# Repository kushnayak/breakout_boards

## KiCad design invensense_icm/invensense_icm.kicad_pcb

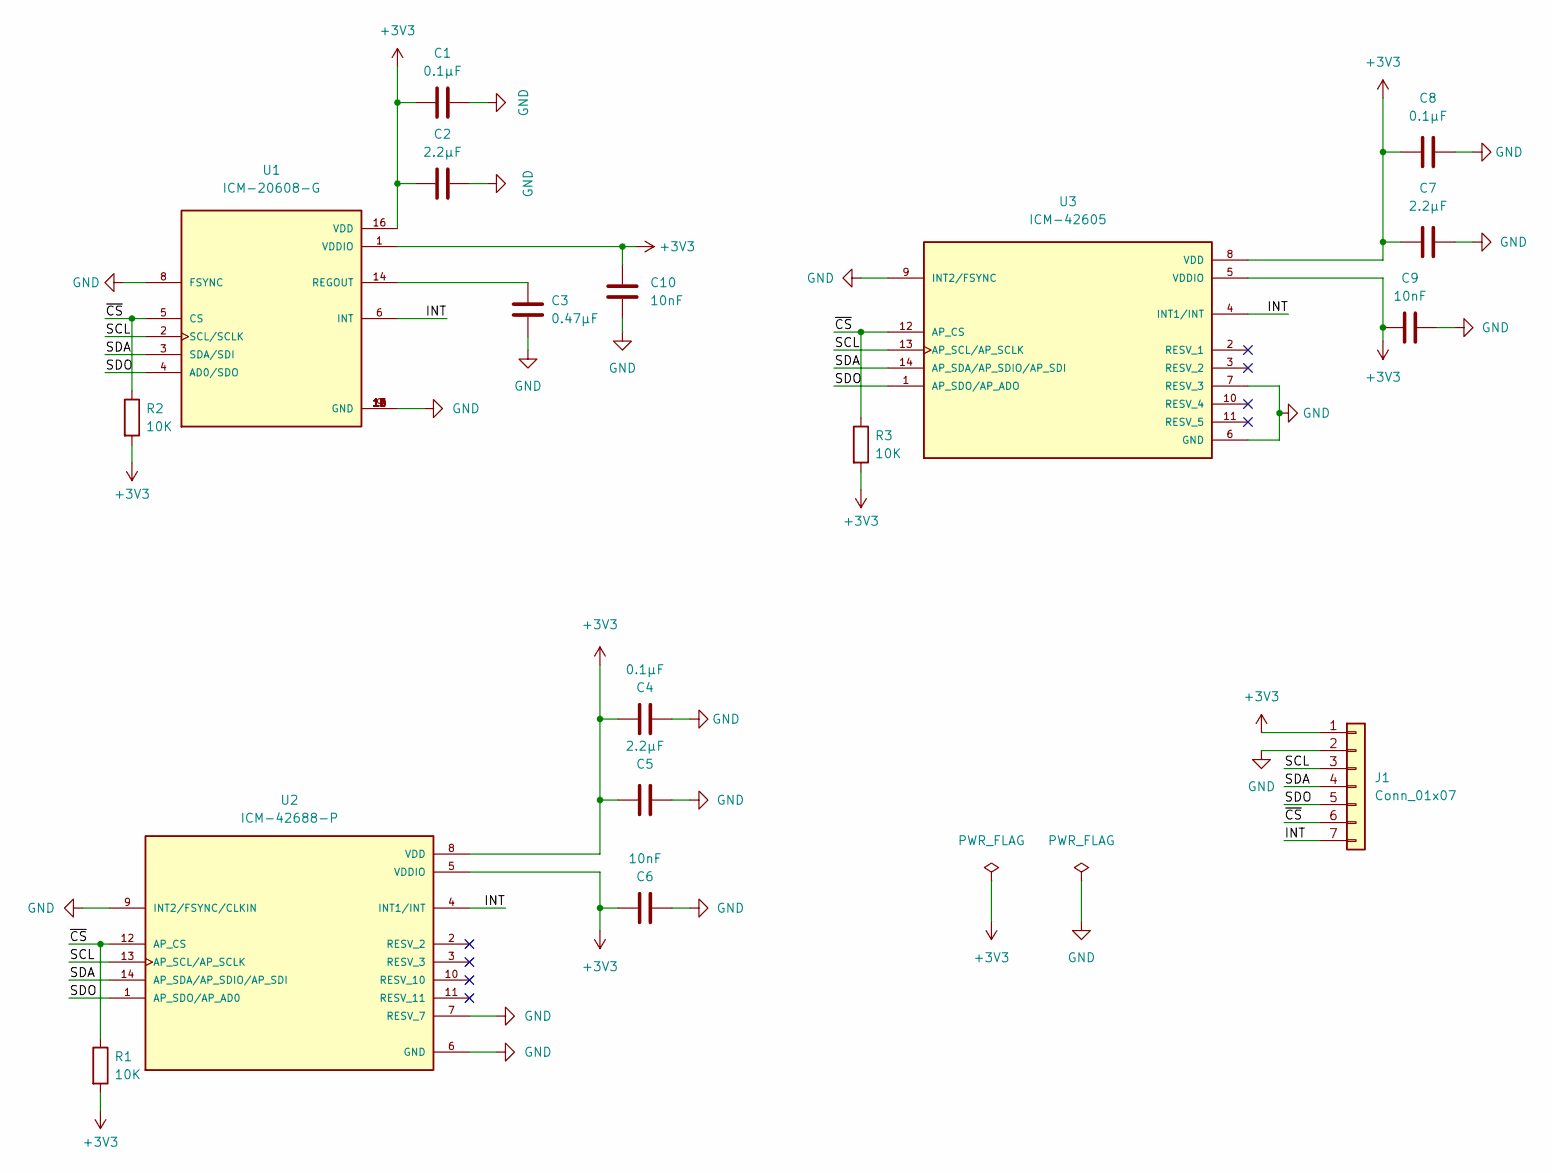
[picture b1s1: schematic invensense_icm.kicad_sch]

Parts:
C1, C4, C8: 0.1µF; C_0603_1608Metric
C2, C5, C7: 2.2µF; C_0603_1608Metric
C3: 0.47µF; C_0603_1608Metric
C6, C9, C10: 10nF; C_0603_1608Metric
J1: Conn_01x07; PinHeader_1x07_P2.54mm_Vertical
R1, R2, R3: 10K; R_0603_1608Metric
U1: ICM-20608-G; PQFN50P300X300X80-16N; PARTREV 1.0
U2: ICM-42688-P; PQFN50P300X250X97-14N; PARTREV 1.2
U3: ICM-42605; PQFN50P300X250X97-14N; PARTREV 0.4

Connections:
+3V3: C1.1, C2.1, C4.2, C5.2, C6.1, C7.2, C8.2, C9.1, C10.1, J1.1, R1.2, R2.2, R3.2, U1.1 (VDDIO), U1.16 (VDD), U2.5 (VDDIO), U2.8 (VDD), U3.5 (VDDIO), U3.8 (VDD)
/INT: J1.7, U1.6 (INT), U2.4 (INT1/INT), U3.4 (INT1/INT)
/SCL: J1.3, U1.2 (SCL/SCLK), U2.13 (AP_SCL/AP_SCLK), U3.13 (AP_SCL/AP_SCLK)
/SDA: J1.4, U1.3 (SDA/SDI), U2.14 (AP_SDA/AP_SDIO/AP_SDI), U3.14 (AP_SDA/AP_SDIO/AP_SDI)
/SDO: J1.5, U1.4 (AD0/SDO), U2.1 (AP_SDO/AP_AD0), U3.1 (AP_SDO/AP_ADO)
/~CS: J1.6, R1.1, R2.1, R3.1, U1.5 (CS), U2.12 (AP_CS), U3.12 (AP_CS)
GND: C1.2, C2.2, C3.1, C4.1, C5.1, C6.2, C7.1, C8.1, C9.2, C10.2, J1.2, U1.8 (FSYNC), U1.9 (GND), U1.10 (GND), U1.11 (GND), U1.12 (GND), U1.13 (GND), U1.15 (GND), U2.6 (GND), U2.7 (RESV_7), U2.9 (INT2/FSYNC/CLKIN), U3.6 (GND), U3.7 (RESV_3), U3.9 (INT2/FSYNC)
unnamed: C3.2, U1.14 (REGOUT)

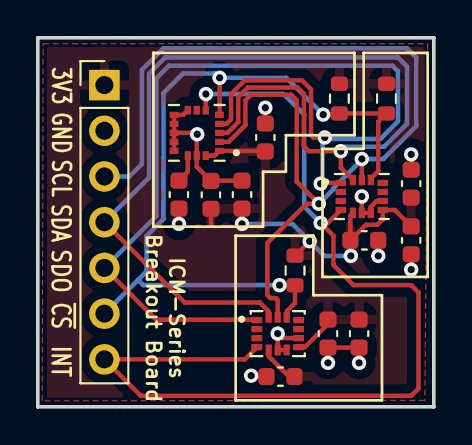
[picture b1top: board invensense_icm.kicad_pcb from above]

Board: 2 copper layers, 22.0 x 20.5 mm, 17 parts (0 on the bottom side), 8 nets.

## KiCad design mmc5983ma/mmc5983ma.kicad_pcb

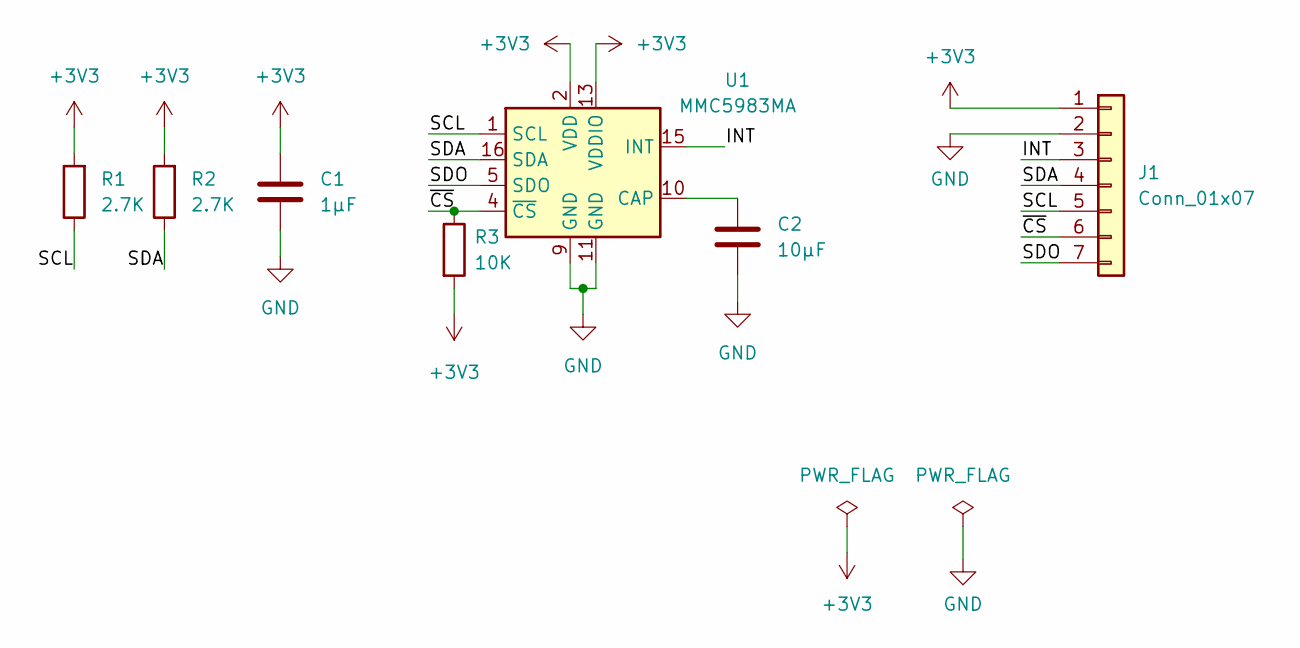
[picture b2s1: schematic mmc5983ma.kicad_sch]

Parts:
C1: 1µF; C_0603_1608Metric
C2: 10µF; C_0603_1608Metric
J1: Conn_01x07; PinHeader_1x07_P2.54mm_Vertical
R1, R2: 2.7K; R_0603_1608Metric
R3: 10K; R_0603_1608Metric
U1: MMC5983MA; LGA-16_3x3mm_P0.5mm

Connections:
+3V3: C1.1, J1.1, R1.2, R2.2, R3.2, U1.2 (VDD), U1.13 (VDDIO)
/INT: J1.3, U1.15 (INT)
/SCL: J1.5, R1.1, U1.1 (SCL)
/SDA: J1.4, R2.1, U1.16 (SDA)
/SDO: J1.7, U1.5 (SDO)
/~CS: J1.6, R3.1, U1.4 (~CS)
GND: C1.2, C2.2, J1.2, U1.9 (GND), U1.11 (GND)
unnamed: C2.1, U1.10 (CAP)

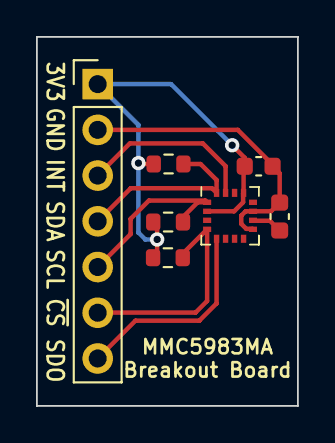
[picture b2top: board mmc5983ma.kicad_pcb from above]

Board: 2 copper layers, 14.5 x 20.5 mm, 7 parts (0 on the bottom side), 8 nets.

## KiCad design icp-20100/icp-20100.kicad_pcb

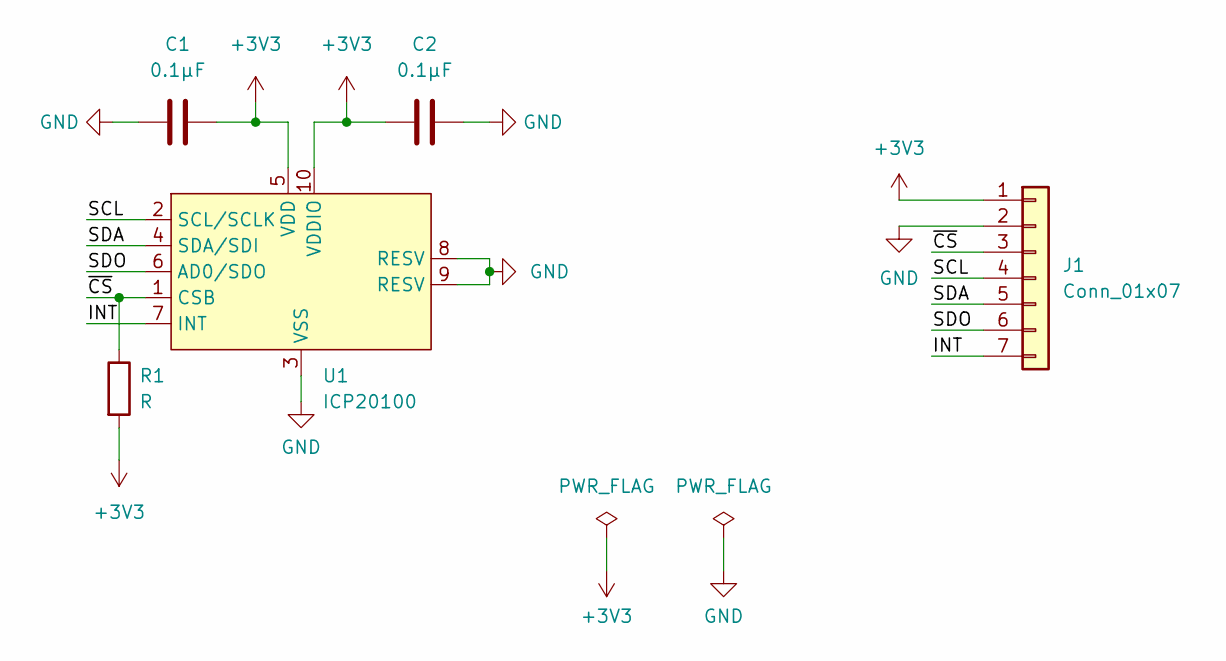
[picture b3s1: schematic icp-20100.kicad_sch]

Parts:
C1, C2: 0.1µF; C_0603_1608Metric
J1: Conn_01x07; PinHeader_1x07_P2.54mm_Vertical
R1: R; R_0603_1608Metric
U1: ICP20100; PQFN50P200X200X85-10N

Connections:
+3V3: C1.2, C2.1, J1.1, R1.2, U1.5 (VDD), U1.10 (VDDIO)
/INT: J1.7, U1.7 (INT)
/SCL: J1.4, U1.2 (SCL/SCLK)
/SDA: J1.5, U1.4 (SDA/SDI)
/SDO: J1.6, U1.6 (AD0/SDO)
/~CS: J1.3, R1.1, U1.1 (CSB)
GND: C1.1, C2.2, J1.2, U1.3 (VSS), U1.8 (RESV), U1.9 (RESV)

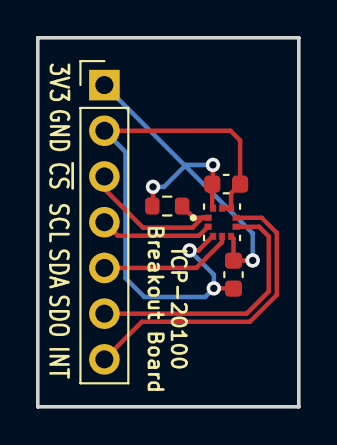
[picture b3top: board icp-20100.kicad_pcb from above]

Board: 2 copper layers, 14.5 x 20.5 mm, 5 parts (0 on the bottom side), 7 nets.

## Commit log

2022-08-15 Slight modification to mmc and add ICP-20100
2022-08-17 Add invensense ICM series board
2022-08-18 Slight modifications to boards and add export files
